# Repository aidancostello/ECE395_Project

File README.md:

# ECE395_Project

See report for directory layout and other information.

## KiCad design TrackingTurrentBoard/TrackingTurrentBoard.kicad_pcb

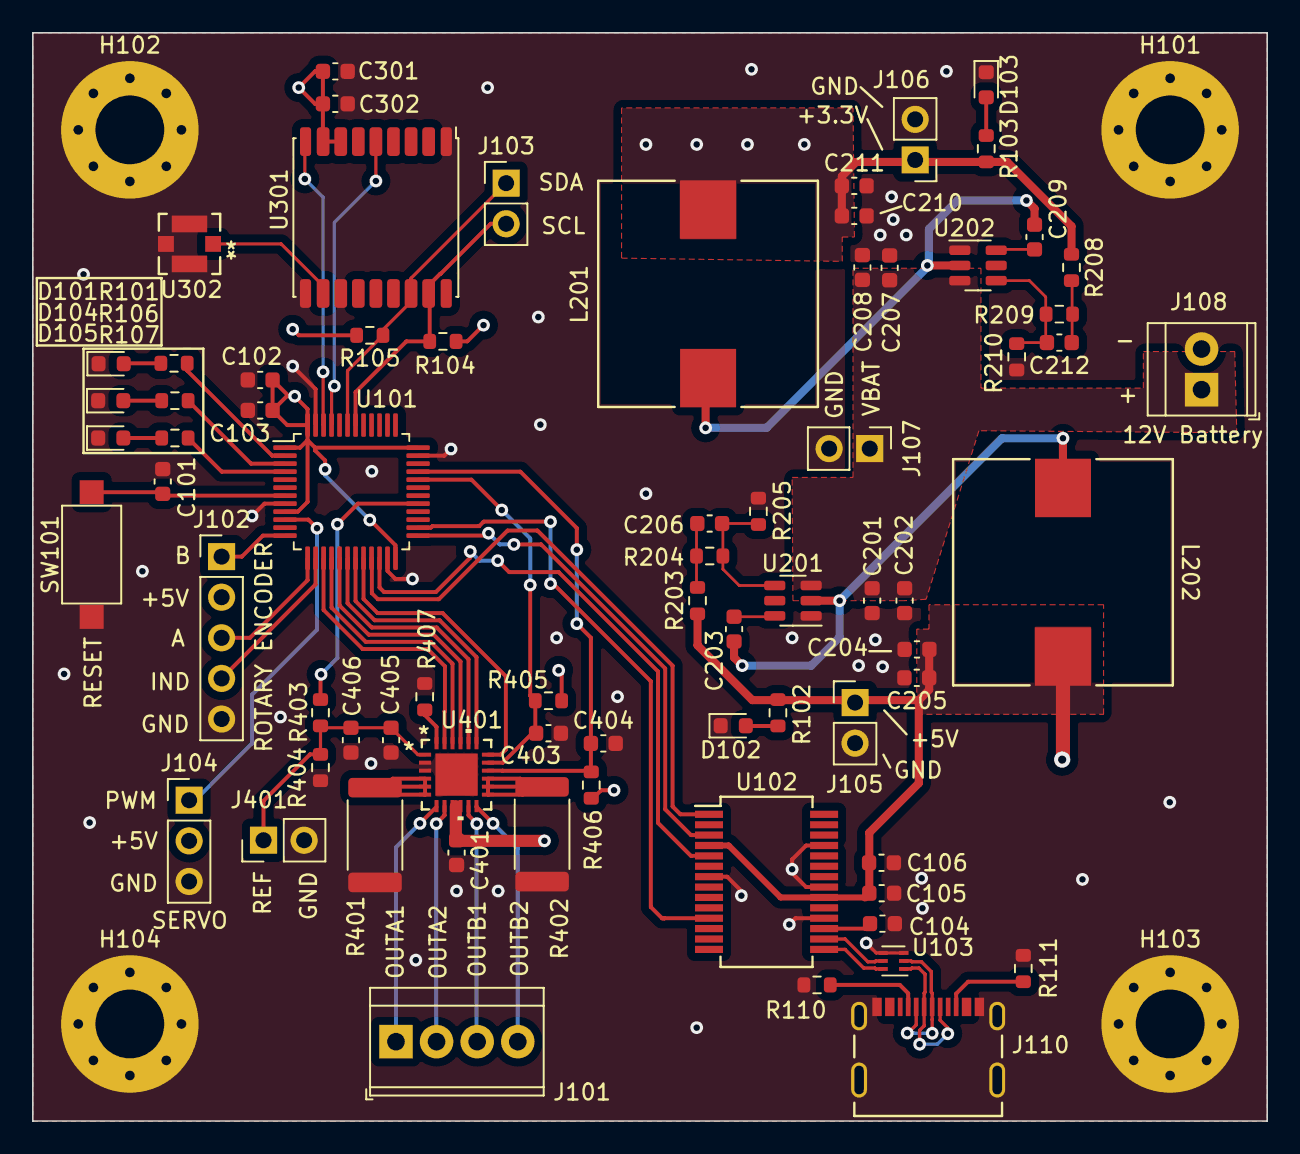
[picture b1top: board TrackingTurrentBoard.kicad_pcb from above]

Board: 4 copper layers, 77.2 x 68.1 mm, 77 parts (0 on the bottom side), 58 nets.

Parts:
C101, C201, C203, C208, C209: 0.1uF; C_0603_1608Metric
C102, C104, C105, C301, C405: 100nF; C_0603_1608Metric
C103, C302, C406: 1uF; C_0603_1608Metric
C106: 4.7uF; C_0603_1608Metric
C202, C207: 10uF; C_0603_1608Metric
C204, C205, C210, C211: 22uF; C_0603_1608Metric
C206: 75pF; C_0603_1608Metric
C212: 43pF; C_0603_1608Metric
C401: 330nF; C_0603_1608Metric
C403: 10nF; C_0603_1608Metric
C404: 1nF; C_0603_1608Metric
D101, D102, D103, D104, D105: LED; LED_0603_1608Metric
H101, H102, H103, H104: M4; MountingHole_4.3mm_M4_Pad_Via
J101: Screw_Terminal_01x04; TerminalBlock_TE_282834-4_1x04_P2.54mm_Horizontal
J102: Conn_01x05; PinHeader_1x05_P2.54mm_Vertical
J103, J105, J106, J107, J401: Conn_01x02; PinHeader_1x02_P2.54mm_Vertical
J104: Conn_01x03; PinHeader_1x03_P2.54mm_Vertical
J108: Screw_Terminal_01x02; TerminalBlock_TE_282834-2_1x02_P2.54mm_Horizontal
J110: 2171790001; MOLEX_2171790001
L201: 6.8uH; IND_BOURNS_SRP1250
L202: 10uH; IND_BOURNS_SRP1250
R101, R102, R103, R106, R107: 100; R_0603_1608Metric
R104, R105: 4.7k; R_0603_1608Metric
R110, R111: 5.1k; R_0603_1608Metric
R203, R208: 50; R_0603_1608Metric
R204, R209: 100k; R_0603_1608Metric
R205: 13.3k; R_0603_1608Metric
R210: 22.1k; R_0603_1608Metric
R401, R402: 330m; R_2512_6332Metric
R403: 2.3k; R_0603_1608Metric
R404: 1k; R_0603_1608Metric
R405: 39k; R_0603_1608Metric
R406: 18k; R_0603_1608Metric
R407: 10k; R_0603_1608Metric
SW101: SW_MEC_5G; SW_SPST_CK_RS282G05A3
U101: STM32L433CCTx; LQFP-48_7x7mm_P0.5mm
U102: FT232RL; SSOP-28_5.3x10.2mm_P0.65mm
U103: ECMF02-2AMX6; ST_UQFN-6L_1.5x1.7mm_P0.5mm
U201, U202: TPS54302; SOT-23-6
U301: MAX-M8C; ublox_MAX
U302: 734120114; 73412-0114_MOL
U401: STSPIN820; QFN_SPIN820_STM

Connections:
+3.3V: C102.1, C103.1, C210.1, C211.1, C301.1, C302.1, J106.1, L201.2, R103.2, R104.2, R105.2, R208.1, R405.1, R406.1, U101.1 (VBAT), U101.9 (VDDA), U101.24 (VDD), U101.36 (VDDUSB), U101.48 (VDD), U301.7 (VCC_IO), U301.8 (VCC)
+5V: C105.1, C106.1, C204.1, C205.1, J102.2, J104.2, J105.1, L202.2, R102.2, R203.1, U102.4 (VCCIO), U102.20 (VCC)
/CHANNEL_A: J102.3, U101.13 (PA3)
/CHANNEL_B: J102.1, U101.12 (PA2)
/DECAY: U101.20 (PB2), U401.18 (DECAY)
/DIR: U101.18 (PB0), U401.20 (DIR)
/EN\FAULT: C403.1, R405.2, U101.32 (PA11), U401.17 (EN\FAULT)
/FTDI_CTS: U101.26 (PB13), U102.11 (CTS)
/FTDI_RTS: U101.25 (PB12), U102.3 (RTS)
/FTDI_RX: U101.22 (PB11), U102.5 (RXD)
/FTDI_TX: U101.21 (PB10), U102.1 (TXD)
/GPS_INT: U101.45 (PB8), U301.5 (EXTINT)
/GPS_RST: U101.46 (PB9), U301.9 (~RESET)
/INDEX: J102.4, U101.14 (PA4)
/LED1: R101.2, U101.2 (PC13)
/LED2: R106.2, U101.3 (PC14)
/LED3: R107.2, U101.4 (PC15)
/MODE1: U101.17 (PA7), U401.21 (MODE1)
/MODE2: U101.16 (PA6), U401.22 (MODE2)
/MODE3: U101.15 (PA5), U401.23 (MODE3)
/Motors/OUTA1: J101.1, U401.7 (OUTA1)
/Motors/OUTA2: J101.2, U401.8 (OUTA2)
/Motors/OUTB1: J101.3, U401.11 (OUTB2)
/Motors/OUTB2: J101.4, U401.12 (OUTB1)
/SCL: J103.2, R104.1, U101.42 (PB6), U301.17 (SCL)
/SDA: J103.1, R105.1, U101.43 (PB7), U301.16 (SDA)
/SERVO_PWM: J104.1, U101.10 (PA0)
/STBY\RST: C404.1, R406.2, U101.33 (PA12), U401.16 (STBY\RESET)
/STCK: U101.19 (PB1), U401.19 (STCK)
/STEP_PWM: R403.1, U101.29 (PA8)
/USB+: J110.A6 (DP1), J110.B6 (DP2), U103.1 (D+_in)
/USB-: J110.A7 (DN1), J110.B7 (DN2), U103.2 (D-_in)
/USB_ESD+: U102.15 (USBD+), U103.6 (D+_out)
/USB_ESD-: U102.16 (USBD-), U103.5 (D-_out)
GND: C101.2, C102.2, C103.2, C104.2, C105.2, C106.2, C201.2, C202.2, C204.2, C205.2, C207.2, C208.2, C210.2, C211.2, C301.2, C302.2, C401.2, C403.2, C404.2, C405.2, C406.2, D101.1 (K), D102.1 (K), D103.1 (K), D104.1 (K), D105.1 (K), H101.1, H102.1, H103.1, H104.1, J102.5, J104.3, J105.2, J106.2, J107.2, J108.2, J110.A1B12 (GND1), J110.B1A12 (GND2), J110.SH1 (SHIELD1), J110.SH2 (SHIELD2), J110.SH3 (SHIELD3), J110.SH4 (SHIELD4), J401.2, R110.1, R111.2, R205.2, R210.2, R401.2, R402.2, R404.2, R407.2, SW101.1 (A), U101.8 (VSSA), U101.23 (VSS), U101.35 (VSS), U101.47 (VSS), U102.7 (GND), U102.18 (GND), U102.21 (GND), U102.25 (AGND), U103.3 (GND), U103.4 (NC), U201.1 (GND), U202.1 (GND), U301.1 (GND), U301.10 (GND), U301.12 (GND), U302.2 (GROUND), U302.3 (GROUND), U302.4 (GROUND), U401.2 (GND), U401.3 (GND), U401.25 (EPAD)
unnamed: C206.1, R203.2, R204.1
unnamed: C212.1, R208.2, R209.1
unnamed: D101.2 (A), R101.1
unnamed: D102.2 (A), R102.1
unnamed: D103.2 (A), R103.1
unnamed: D104.2 (A), R106.1
unnamed: D105.2 (A), R107.1
unnamed: J110.A5 (CC1), R110.2
unnamed: J110.B5 (CC2), R111.1
unnamed: C405.1, C406.1, J401.1, R403.2, R404.1, U401.1 (REF)
unnamed: C101.1, SW101.2 (B), U101.7 (NRST)
unnamed: C104.1, U102.17 (3V3OUT)
unnamed: C203.1, U201.6 (BOOT)
unnamed: C206.2, R204.2, R205.1, U201.4 (FB)
unnamed: C203.2, L202.1, U201.2 (SW)
unnamed: C209.1, U202.6 (BOOT)
unnamed: C212.2, R209.2, R210.1, U202.4 (FB)
unnamed: C209.2, L201.1, U202.2 (SW)
unnamed: U301.11 (RF_IN), U302.1 (SIGNAL)
unnamed: R401.1, U401.4 (SNSA), U401.5 (SENSEA1), U401.6 (SENSEA2)
unnamed: R402.1, U401.13 (SENSEB2), U401.14 (SENSEB1), U401.15 (SNSB)
unnamed: R407.1, U401.24 (TOFF)
VBUS: C201.1, C202.1, C207.1, C208.1, C401.1, J107.1, J108.1, U201.3 (VIN), U202.3 (VIN), U401.9 (VS), U401.10 (VS)

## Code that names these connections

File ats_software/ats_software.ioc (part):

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Mcu.Name=STM32L433C(B-C)Tx
Mcu.Package=LQFP48
Mcu.UserName=STM32L433CCTx
PA0.Signal=S_TIM2_CH1
PA11.Signal=GPIO_Output
PA12.Signal=GPIO_Output
PA2.Signal=GPIO_Input
PA3.Signal=GPIO_Input
PA4.Signal=GPIO_Input
PA5.Signal=GPIO_Output
PA6.Signal=GPIO_Output
PA7.Signal=GPIO_Output
PA8.Signal=GPIO_Output
PB0.Signal=GPIO_Output
PB1.Signal=GPIO_Output
PB10.Mode=Asynchronous
PB10.Signal=USART3_TX
PB11.Mode=Asynchronous
PB11.Signal=USART3_RX
PB12.Signal=GPIO_Output
PB13.Signal=GPIO_Output
PB2.Signal=GPIO_Output
PB6.Mode=I2C
PB6.Signal=I2C1_SCL
PB7.Mode=I2C
PB7.Signal=I2C1_SDA
PB8.Signal=GPIO_Input
PB9.Signal=GPIO_Output
PC13.Signal=GPIO_Output
PC14-OSC32_IN\ (PC14).Signal=GPIO_Output
PC15-OSC32_OUT\ (PC15).Signal=GPIO_Output
RCC.HSE_VALUE=8000000
board=custom

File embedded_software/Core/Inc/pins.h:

#ifndef __PINS_H
#define __PINS_H

// ***** LEDS *****
// LED1
#define LED1_BANK GPIOC
#define LED1_PIN GPIO_PIN_13
// LED2
#define LED2_BANK GPIOC
#define LED2_PIN GPIO_PIN_14
// LED3
#define LED3_BANK GPIOC
#define LED3_PIN GPIO_PIN_15

// ***** GPS *****
// reset
#define GPS_RESET_BANK GPIOA
#define GPS_RESET_PIN GPIO_PIN_9
// interrupt
#define GPS_INT_BANK GPIOA
#define GPS_INT_PIN GPIO_PIN_8

// ***** STEPPER *****
// reset
#define STEPPER_RESET_BANK GPIOA
#define STEPPER_RESET_PIN GPIO_PIN_12
// enable
#define STEPPER_EN_BANK GPIOA
#define STEPPER_EN_PIN GPIO_PIN_11
// step
#define STEPPER_STCK_BANK GPIOB
#define STEPPER_STCK_PIN GPIO_PIN_1
// dir
#define STEPPER_DIR_BANK GPIOB
#define STEPPER_DIR_PIN GPIO_PIN_0
// decay
#define STEPPER_DECAY_BANK GPIOB
#define STEPPER_DECAY_PIN GPIO_PIN_2
// mode1
#define STEPPER_MODE1_BANK GPIOA
#define STEPPER_MODE1_PIN GPIO_PIN_7
// mode2
#define STEPPER_MODE2_BANK GPIOA
#define STEPPER_MODE2_PIN GPIO_PIN_6
// mode3
#define STEPPER_MODE3_BANK GPIOA
#define STEPPER_MODE3_PIN GPIO_PIN_5
// pwm
#define STEPPER_PWM_BANK GPIOA
#define STEPPER_PWM_PIN GPIO_PIN_8

// ***** UART *****
// rts
#define UART_RTS_BANK GPIOB
#define UART_RTS_PIN GPIO_PIN_12
// cts
#define UART_CTS_BANK GPIOB
#define UART_CTS_PIN GPIO_PIN_13

// ***** ENCODER ******
// channel a
#define ENCODER_CHANNEL_A_BANK GPIOA
#define ENCODER_CHANNEL_A_PIN GPIO_PIN_3
// channel b
#define ENCODER_CHANNEL_B_BANK GPIOA
#define ENCODER_CHANNEL_B_PIN GPIO_PIN_2
// index
#define ENCODER_INDEX_BANK GPIOA
#define ENCODER_INDEX_PIN GPIO_PIN_4

#endif

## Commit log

2024-09-04 inital KiCad project added
2024-09-06 added symbols and started power circuits
2024-09-11 added buck sch
2024-10-22 added files
2024-10-22 updated file structure
2024-10-22 updated pin definitions
2024-10-25 python tests for stepper and calculations
2024-10-25 barebones uart receiving
2024-10-31 PCB done
2024-11-05 added uart mutex
2024-11-12 uart receive dma
2024-11-16 fixed mutex issue, added logging library
2024-11-16 logging lib changes
2024-11-16 fixed PI bug
2024-11-19 added better log infrastructure
2024-11-19 updated logging
2024-11-21 switched to lpuart1
2024-11-21 green blink
2024-12-04 working on benchtop
2024-12-04 interactive demo barebones
2024-12-04 commented out encoder thread, not necessary
2024-12-04 restructure
2024-12-05 finished demo scripts
2024-12-05 adjusted constants, labeled units
2024-12-17 most recent pcb and sch
2024-12-17 removed .lcks
